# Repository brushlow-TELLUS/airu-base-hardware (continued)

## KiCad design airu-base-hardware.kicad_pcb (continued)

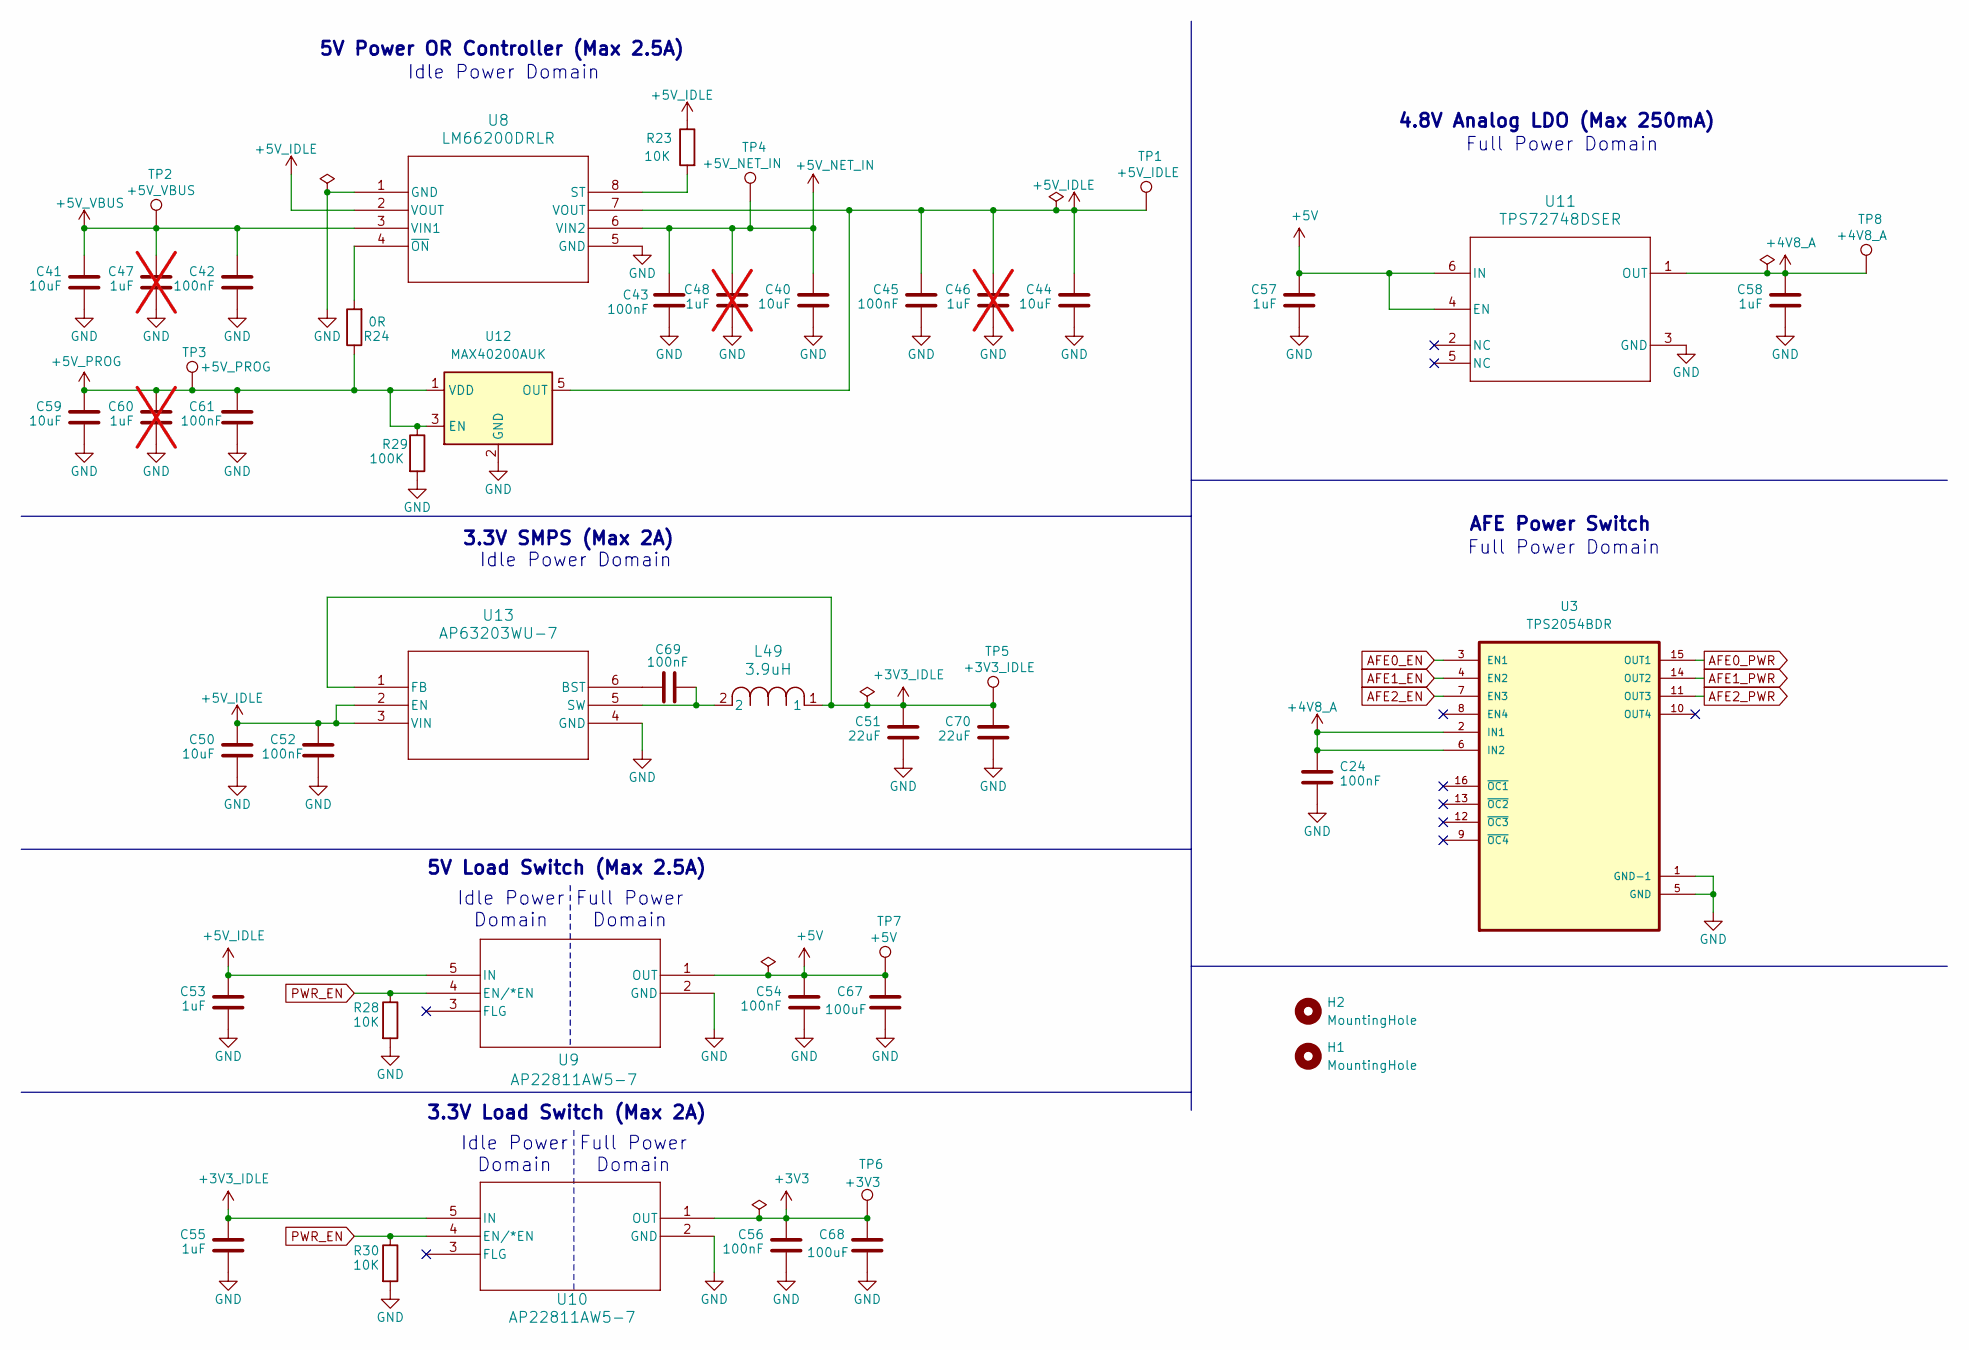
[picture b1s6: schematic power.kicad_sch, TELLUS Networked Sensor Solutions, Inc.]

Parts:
C24, C42, C43, C45, C52, C54, C56, C61, C69: 100nF; C_0603_1608Metric; Manufacturer_PN CC0603KRX7R7BB104
C40, C41, C44, C50, C59: 10uF; C_0603_1608Metric; Manufacturer_PN CL10X106MO8NRNC
C46, C47, C48, C60: 1uF; C_0603_1608Metric; not fitted
C51, C70: 22uF; C_0603_1608Metric; Manufacturer_PN GRM188R61A226ME15D
C53, C55, C57, C58: 1uF; C_0603_1608Metric; Manufacturer_PN CL10B105KP8NNNC
C67, C68: 100uF; C_1206_3216Metric; Manufacturer_PN GRM31CR61A107MEA8K
H1, H2: MountingHole; MountingHole_3.2mm_M3
L49: 3.9uH; IND_ASPI-0628-3R9M-T1; Manufacturer_PN ASPI-0628-3R9M-T
R23, R28, R30: 10K; R_0603_1608Metric; Manufacturer_PN RC0603FR-0710KL
R24: 0R; R_0603_1608Metric; Manufacturer_PN RC0603JR-070RL
R29: 100K; R_0603_1608Metric; Manufacturer_PN RC0603FR-07100KL
TP1: +5V_IDLE; TestPoint_Pad_1.0x1.0mm
TP2: +5V_VBUS; TestPoint_Pad_1.0x1.0mm
TP3: +5V_PROG; TestPoint_Pad_1.0x1.0mm
TP4: +5V_NET_IN; TestPoint_Pad_1.0x1.0mm
TP5: +3V3_IDLE; TestPoint_Pad_1.0x1.0mm
TP6: +3V3; TestPoint_Pad_1.0x1.0mm
TP7: +5V; TestPoint_Pad_1.0x1.0mm
TP8: +4V8_A; TestPoint_Pad_1.0x1.0mm
U3: TPS2054BDR; SOIC127P600X175-16N; Manufacturer_PN TPS2054BDR
U8: LM66200DRLR; SOT-5X3_DRL_TEX; Manufacturer_PN LM66200DRLR
U9, U10: AP22811AW5-7; AP22811AW5-7_DIO; Manufacturer_PN AP22811AW5-7
U11: TPS72748DSER; DSE0006A; Manufacturer_PN TPS72748DSER
U12: MAX40200AUK; SOT-23-5; Manufacturer_PN MAX40200AUK+T
U13: AP63203WU-7; AP63203WU-7_DIO; Manufacturer_PN AP63203WU-7

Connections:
+3V3: C56.1, C68.1, TP6.1, U10.1 (OUT); also elsewhere on the board
+3V3_IDLE: C51.1, C55.1, C70.1, L49.1, TP5.1, U10.5 (IN), U13.1 (FB); also elsewhere on the board
+4V8_A: C24.1, C58.1, TP8.1, U3.2 (IN1), U3.6 (IN2), U11.1 (OUT); also elsewhere on the board
+5V: C54.1, C57.1, C67.1, TP7.1, U9.1 (OUT), U11.4 (EN), U11.6 (IN); also elsewhere on the board
+5V_IDLE: C44.1, C45.1, C46.1, C50.1, C52.1, C53.1, R23.1, TP1.1, U8.2 (VOUT), U8.7 (VOUT), U9.5 (IN), U12.5 (OUT), U13.2 (EN), U13.3 (VIN); also elsewhere on the board
+5V_NET_IN: C40.1, C43.1, C48.1, TP4.1, U8.6 (VIN2); also elsewhere on the board
+5V_PROG: C59.1, C60.1, C61.1, R24.1, R29.1, TP3.1, U12.1 (VDD), U12.3 (EN); also elsewhere on the board
+5V_VBUS: C41.1, C42.1, C47.1, TP2.1, U8.3 (VIN1); also elsewhere on the board
AFE0_EN: U3.3 (EN1); also elsewhere on the board
AFE0_PWR: U3.15 (OUT1); also elsewhere on the board
AFE1_EN: U3.4 (EN2); also elsewhere on the board
AFE1_PWR: U3.14 (OUT2); also elsewhere on the board
AFE2_EN: U3.7 (EN3); also elsewhere on the board
AFE2_PWR: U3.11 (OUT3); also elsewhere on the board
GND: C24.2, C40.2, C41.2, C42.2, C43.2, C44.2, C45.2, C46.2, C47.2, C48.2, C50.2, C51.2, C52.2, C53.2, C54.2, C55.2, C56.2, C57.2, C58.2, C59.2, C60.2, C61.2, C67.2, C68.2, C70.2, R28.2, R29.2, R30.2, U3.1 (GND-1), U3.5 (GND), U8.1 (GND), U8.5 (GND), U9.2 (GND), U10.2 (GND), U11.3 (GND), U12.2 (GND), U13.4 (GND); also elsewhere on the board
unnamed: R23.2, U8.8 (ST)
unnamed: R24.2, U8.4 (~ON)
unnamed: C69.1, U13.6 (BST)
unnamed: C69.2, L49.2, U13.5 (SW)
PWR_EN: R28.1, R30.1, U9.4 (EN/*EN), U10.4 (EN/*EN); also elsewhere on the board

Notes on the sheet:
Full Power Domain
4.8V Analog LDO (Max 250mA)
5V Power OR Controller (Max 2.5A)
Full Power Domain
Idle Power Domain
Idle Power Domain
3.3V Load Switch (Max 2A)
AFE Power Switch
5V Load Switch (Max 2.5A)
3.3V SMPS (Max 2A)

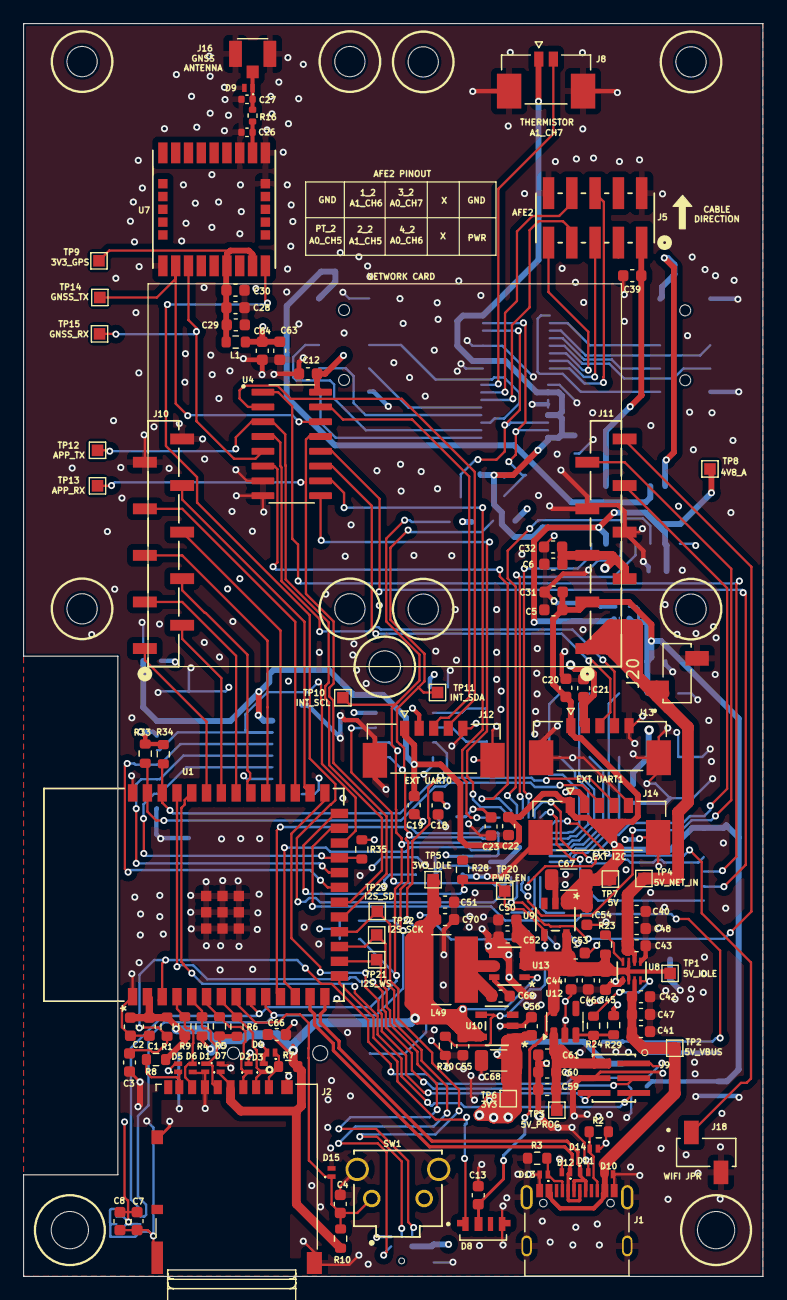
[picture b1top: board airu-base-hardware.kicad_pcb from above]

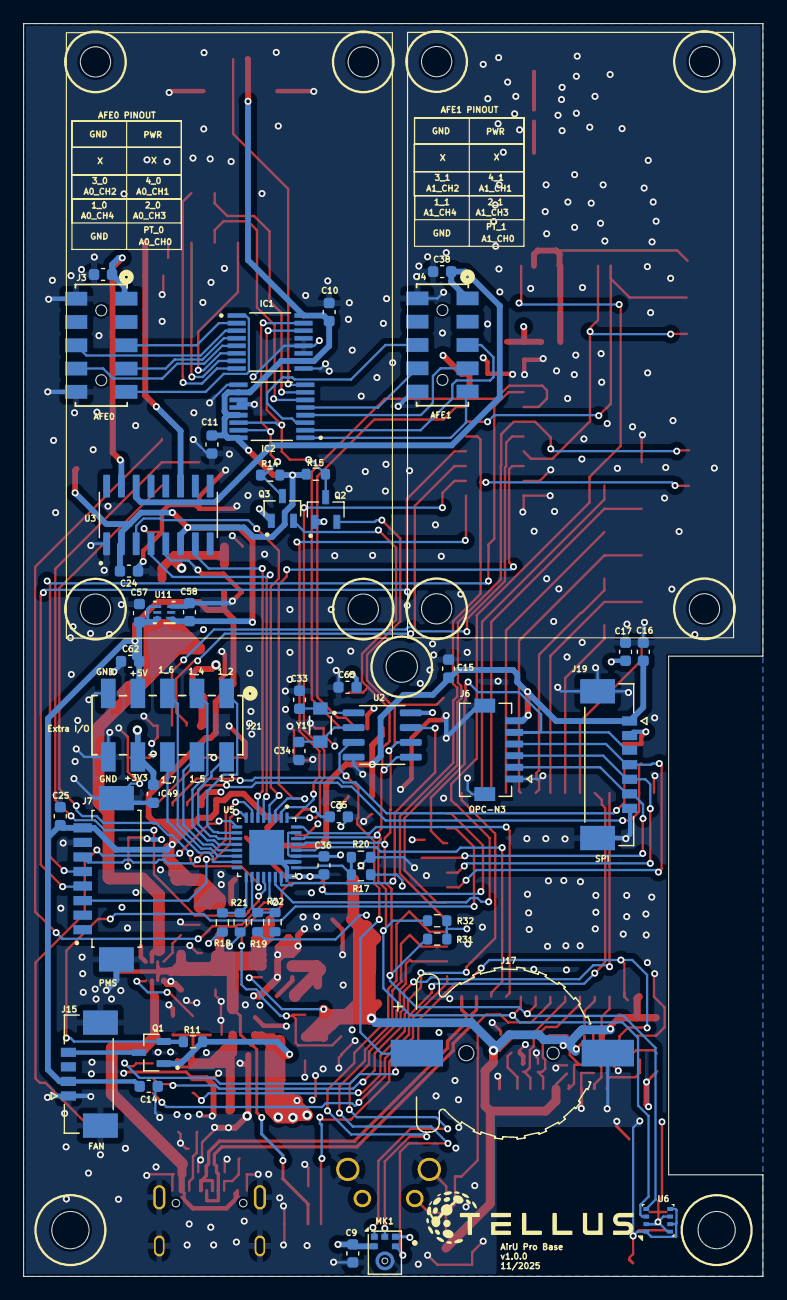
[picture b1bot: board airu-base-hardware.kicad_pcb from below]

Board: 4 copper layers, 63.5 x 107.6 mm, 181 parts (51 on the bottom side), 113 nets.

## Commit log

2025-10-09 Initial commit; schematic under review
2025-10-23 Layout draft
2025-10-27 Refine layout
2025-10-29 More mfg readiness tweaks; ext power hdr
2025-11-14 Tweaks
